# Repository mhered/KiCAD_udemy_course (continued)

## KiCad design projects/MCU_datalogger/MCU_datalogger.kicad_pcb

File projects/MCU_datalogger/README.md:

# README.md

A simple **microcontroller-based datalogger** designed to practice PCB design in KiCAD while introducing the fundamentals of embedded data acquisition. The board reads sensor data through the MCU and stores it in EEPROM, making it possible to log measurements over time.

The design covers the key building blocks of a typical datalogger system:

- **MCU (microcontroller)** – handles sensor interfacing, data collection, and storage management.
- **Sensors / Inputs** – generic sensor connections to capture physical measurements.
- **EEPROM** – nonvolatile memory to store logged data.
- **Power supply** – provides stable operation from external power or batteries.
- **Programming / Debug headers** – for uploading firmware and retrieving logged data (??)

DS1337S

ATMEGA328P-AU from SNAPEDA

## v1.0

## v1.1

Adjust edges and silkscreen, add Vcc fill zone

## Bootloading and firmware uploading the ATMEGA328

- Arduino to atmega328 [Arduino Uno to ATmega328 - Shrinking your Arduino ProjectsYouTube · DroneBot Workshop29 Dec 2018](https://www.youtube.com/watch?v=Sww1mek5rHU)
- Shrinking arduino projects atmega328 https://youtu.be/aex1HFhJG_g?si=vZYHLi1vfadTmJW0

- http://www.kerrywong.com/2010/09/25/i2c-data-logger-using-atmega328p-and-ds3232/

## v1.3

ChatGPT disagrees with the choice of an electrolytic 100nF capacitor in parallel with the battery it says it is too slow. and recommends instead a ceramic 100nF close to the MCU pins to act as filter for spikes. Optionally can add a 10-100uF bulk cap (e.g. electrolytic) to stabilize)

I cant find anything in the datasheet

Looks like EEPROM address is hardcoded 111 and 101, check datasheet!

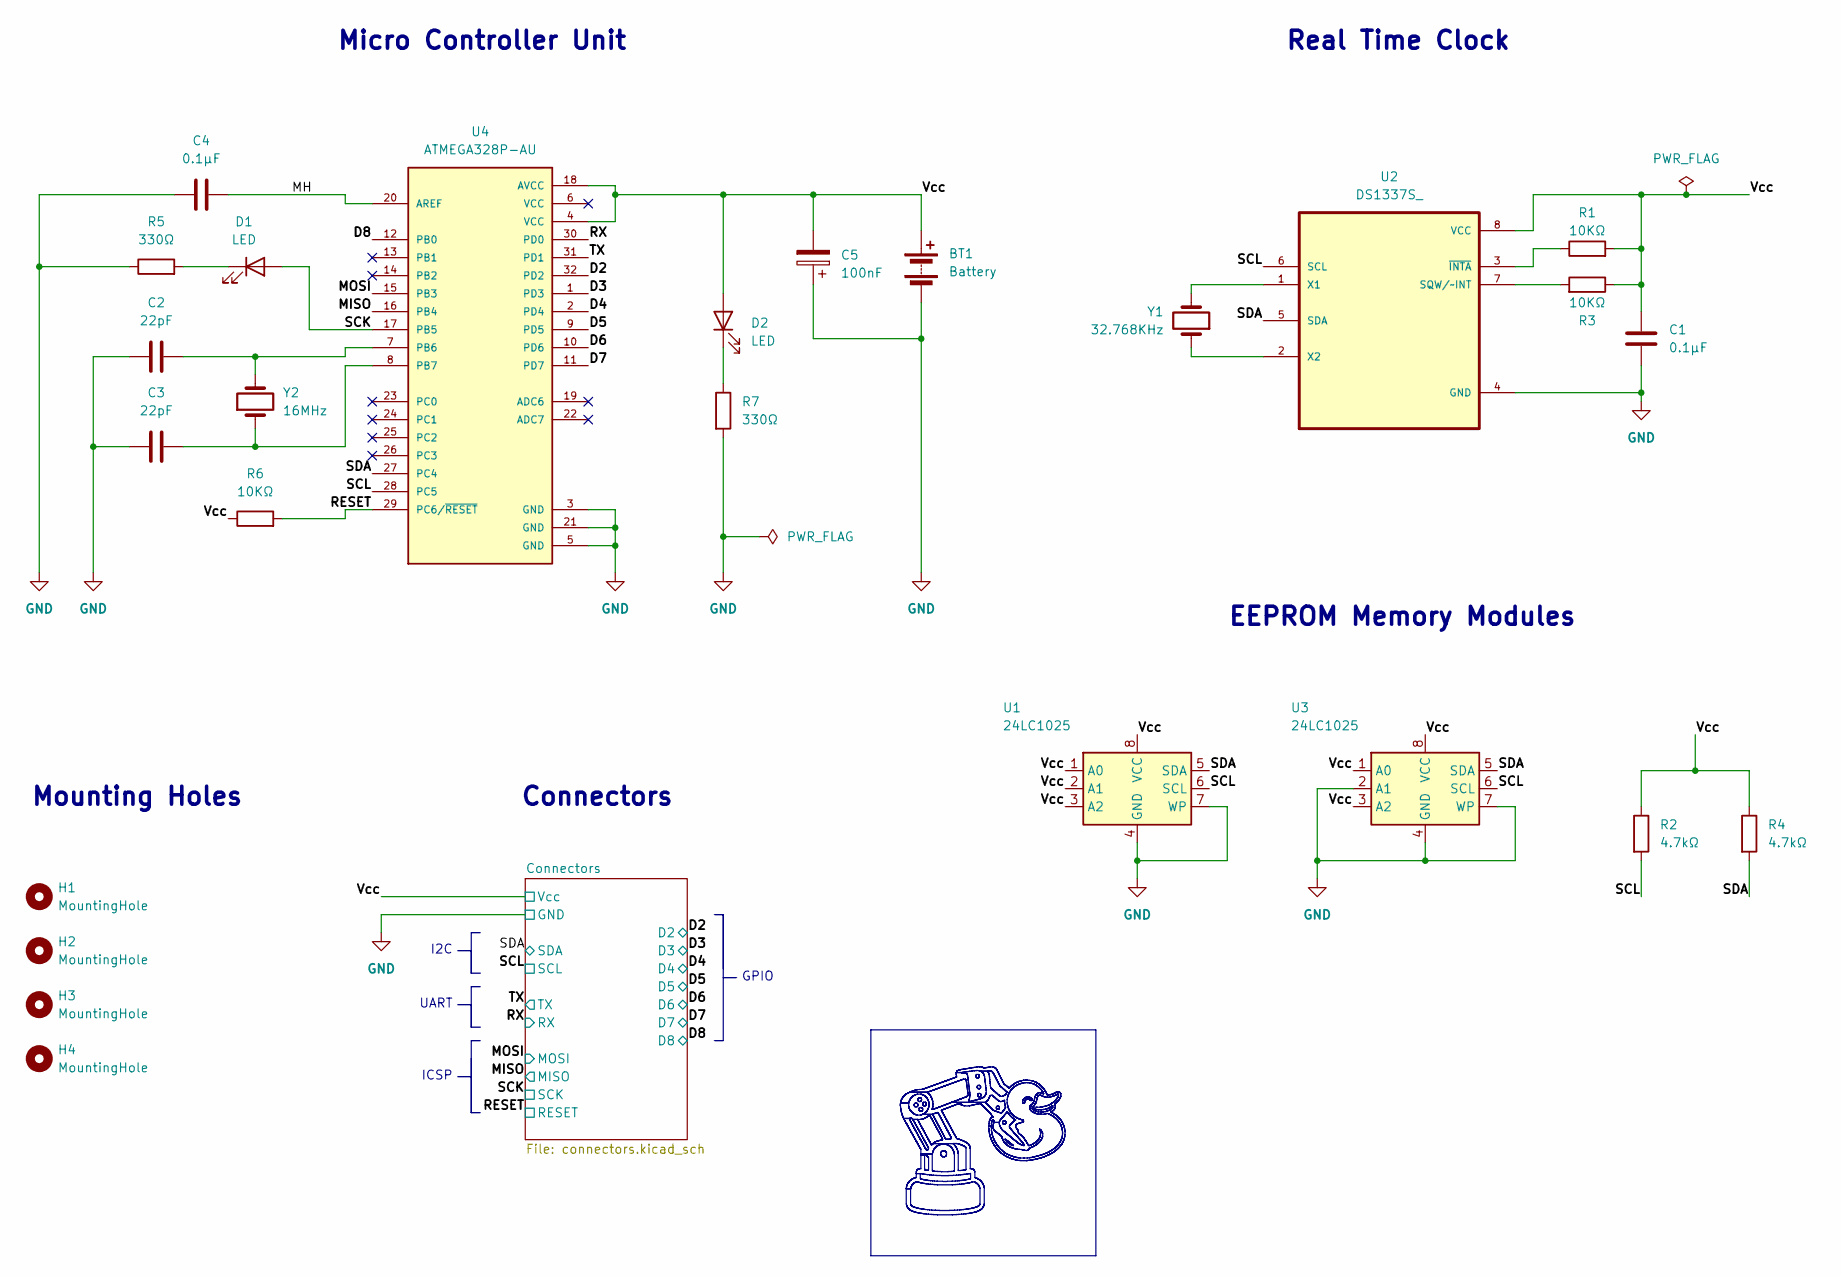
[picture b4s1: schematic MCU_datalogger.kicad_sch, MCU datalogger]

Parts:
BT1: Battery; PinHeader_1x02_P2.54mm_Vertical
C1, C4: 0.1μF; C_1206_3216Metric_Pad1.33x1.80mm_HandSolder
C2, C3: 22pF; C_1206_3216Metric_Pad1.33x1.80mm_HandSolder
C5: 100nF; C_1206_3216Metric_Pad1.33x1.80mm_HandSolder
D1, D2: LED; LED_1206_3216Metric_Pad1.42x1.75mm_HandSolder
H1, H2, H3, H4: MountingHole; MountingHole_2.2mm_M2
R1, R3, R6: 10KΩ; R_1206_3216Metric_Pad1.30x1.75mm_HandSolder
R2, R4: 4.7kΩ; R_1206_3216Metric_Pad1.30x1.75mm_HandSolder
R5, R7: 330Ω; R_1206_3216Metric_Pad1.30x1.75mm_HandSolder
U1, U3: 24LC1025; SOIC-8_5.3x5.3mm_P1.27mm
U2: DS1337S_; SOIC127P600X175-8N
U4: ATMEGA328P-AU; QFP80P900X900X120-32N; PARTREV 8271A
Y1: 32.768KHz; Crystal_SMD_3215-2Pin_3.2x1.5mm
Y2: 16MHz; Crystal_SMD_5032-2Pin_5.0x3.2mm_HandSoldering

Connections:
/D2: U4.32 (PD2); also elsewhere on the board
/D3: U4.1 (PD3); also elsewhere on the board
/D4: U4.2 (PD4); also elsewhere on the board
/D5: U4.9 (PD5); also elsewhere on the board
/D6: U4.10 (PD6); also elsewhere on the board
/D7: U4.11 (PD7); also elsewhere on the board
/D8: U4.12 (PB0); also elsewhere on the board
/MH: C4.2, U4.20 (AREF)
/MISO: U4.16 (PB4); also elsewhere on the board
/MOSI: U4.15 (PB3); also elsewhere on the board
/RESET: R6.2, U4.29 (PC6/~RESET); also elsewhere on the board
/RX: U4.30 (PD0); also elsewhere on the board
/SCK: D1.2 (A), U4.17 (PB5); also elsewhere on the board
/SCL: R2.2, U1.6 (SCL), U2.6 (SCL), U3.6 (SCL), U4.28 (PC5); also elsewhere on the board
/SDA: R4.2, U1.5 (SDA), U2.5 (SDA), U3.5 (SDA), U4.27 (PC4); also elsewhere on the board
/TX: U4.31 (PD1); also elsewhere on the board
/Vcc: BT1.1 (+), C1.1, C5.2, D2.2 (A), R1.2, R2.1, R3.1, R4.1, R6.1, U1.1 (A0), U1.2 (A1), U1.3 (A2), U1.8 (VCC), U2.8 (VCC), U3.1 (A0), U3.3 (A2), U3.8 (VCC), U4.4 (VCC), U4.18 (AVCC); also elsewhere on the board
GND: BT1.2 (-), C1.2, C2.1, C3.1, C4.1, C5.1, R5.1, R7.2, U1.4 (GND), U1.7 (WP), U2.4 (GND), U3.2 (A1), U3.4 (GND), U3.7 (WP), U4.3 (GND), U4.5 (GND), U4.21 (GND); also elsewhere on the board
unnamed: D1.1 (K), R5.2
unnamed: D2.1 (K), R7.1
unnamed: R3.2, U2.7 (SQW/~INT)
unnamed: U2.1 (X1), Y1.2
unnamed: U2.2 (X2), Y1.1
unnamed: R1.1, U2.3 (~INTA)
unnamed: C2.2, U4.7 (PB6), Y2.2
unnamed: C3.2, U4.8 (PB7), Y2.1

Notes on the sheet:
Connectors
Micro Controller Unit
EEPROM Memory Modules
UART
I2C
GPIO
Real Time Clock
Mounting Holes
ICSP

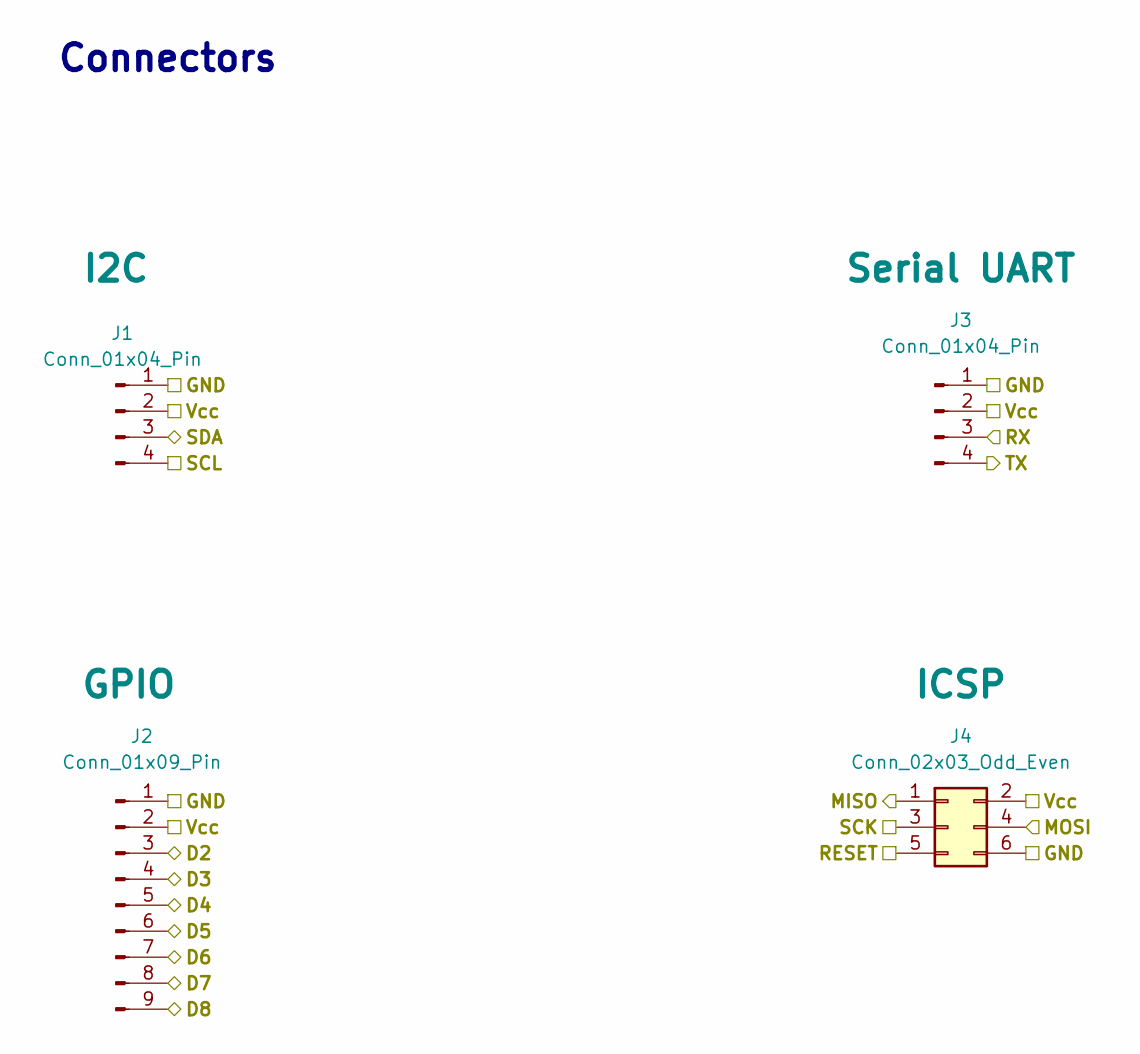
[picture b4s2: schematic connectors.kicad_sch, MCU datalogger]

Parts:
J1, J3: Conn_01x04_Pin; PinHeader_1x04_P2.54mm_Vertical
J2: Conn_01x09_Pin; PinHeader_1x09_P2.54mm_Vertical
J4: Conn_02x03_Odd_Even; PinHeader_2x03_P2.54mm_Vertical

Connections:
/D2: J2.3; also elsewhere on the board
/D3: J2.4; also elsewhere on the board
/D4: J2.5; also elsewhere on the board
/D5: J2.6; also elsewhere on the board
/D6: J2.7; also elsewhere on the board
/D7: J2.8; also elsewhere on the board
/D8: J2.9; also elsewhere on the board
/MISO: J4.1; also elsewhere on the board
/MOSI: J4.4; also elsewhere on the board
/RESET: J4.5; also elsewhere on the board
/RX: J3.3; also elsewhere on the board
/SCK: J4.3; also elsewhere on the board
/SCL: J1.4; also elsewhere on the board
/SDA: J1.3; also elsewhere on the board
/TX: J3.4; also elsewhere on the board
/Vcc: J1.2, J2.2, J3.2, J4.2; also elsewhere on the board
GND: J1.1, J2.1, J3.1, J4.6; also elsewhere on the board

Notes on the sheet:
Connectors

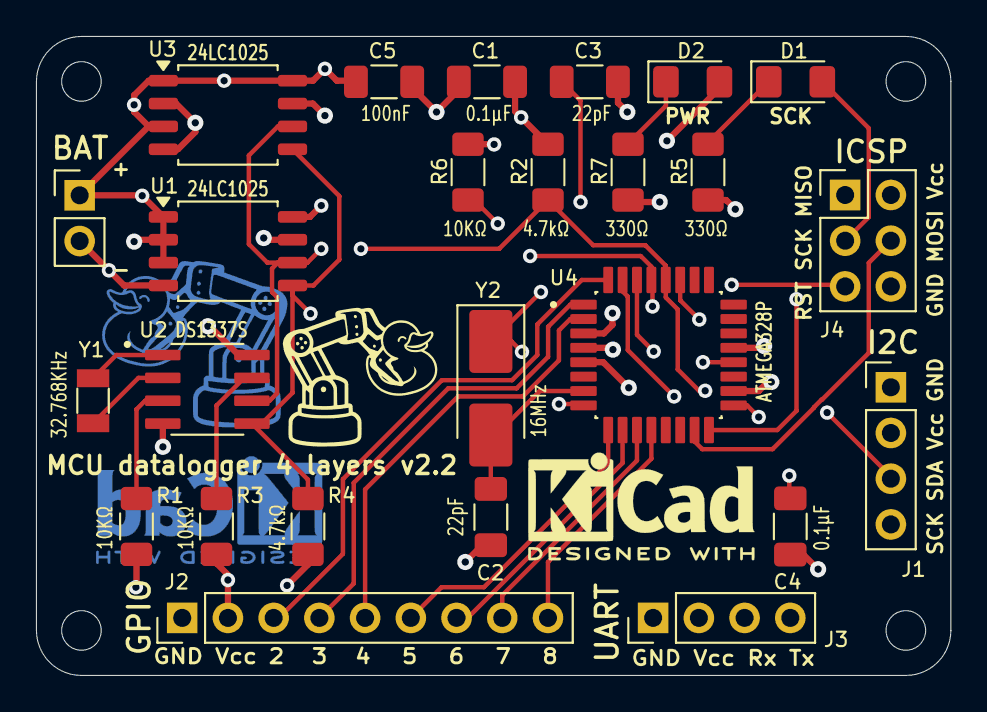
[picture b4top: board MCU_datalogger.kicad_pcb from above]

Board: 4 copper layers, 50.8 x 35.5 mm, 29 parts (0 on the bottom side), 26 nets.

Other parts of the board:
BAT: Battery; PinHeader_1x02_P2.54mm_Vertical

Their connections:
/Vcc: BAT.1 (+); also elsewhere on the board
GND: BAT.2 (-); also elsewhere on the board

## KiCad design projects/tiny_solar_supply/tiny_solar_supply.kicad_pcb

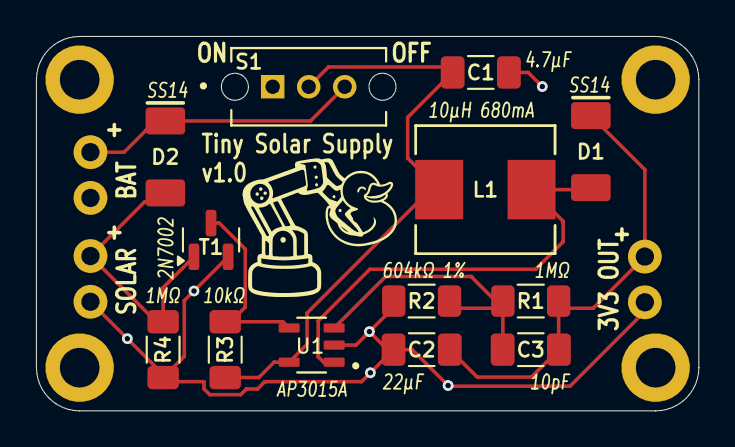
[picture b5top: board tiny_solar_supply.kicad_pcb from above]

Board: 2 copper layers, 36.8 x 20.8 mm, 16 parts (0 on the bottom side), 8 nets.

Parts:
C1: 4.7µF; C_1206_3216Metric_Pad1.33x1.80mm_HandSolder
C2: 22µF; C_1206_3216Metric_Pad1.33x1.80mm_HandSolder
C3: 10pF; C_1206_3216Metric_Pad1.33x1.80mm_HandSolder
D1, D2: SS14; SMA
J1, J2, J4: Conn_01x02; 1x02
L1: 10µH 680mA; IND_ASPI-0630LR_ABR
R1, R4: 1MΩ; R_1206_3216Metric_Pad1.30x1.75mm_HandSolder
R2: 604kΩ 1%; R_1206_3216Metric_Pad1.30x1.75mm_HandSolder
R3: 10kΩ; R_1206_3216Metric_Pad1.30x1.75mm_HandSolder
S1: OS102011MS2QN1; SW_OS102011MS2QN1
T1: 2N7002; SOT-23
U1: AP3015A; SOT95P280X145-5N

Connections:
/BATT_POSITIVE: D2.1 (K), J2.1, S1.3
/OUTPUT_POSITIVE: C2.2, C3.2, D1.1 (K), J1.1, R1.2
/SOLAR_POSITIVE: D2.2 (A), J4.1, R4.2, T1.1 (G)
GNDD: C1.1, C2.1, J1.2, J2.2, J4.2, R2.1, R4.1, T1.2 (S), U1.2 (GND)
unnamed: D1.2 (A), L1.2, U1.1 (SW)
unnamed: R3.1, T1.3 (D), U1.4 (~SHDN)
unnamed: C3.1, R1.1, R2.2, U1.3 (FB)
unnamed: C1.2, L1.1, R3.2, S1.2, U1.5 (VIN)

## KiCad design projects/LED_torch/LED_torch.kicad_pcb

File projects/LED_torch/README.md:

# README.md

## LED_torch - a first basic PCB project 

## Designing the covers

make it clip snuggly while allowing for tolerances, (especially on the soldered components) is fun

## 3D printing the covers

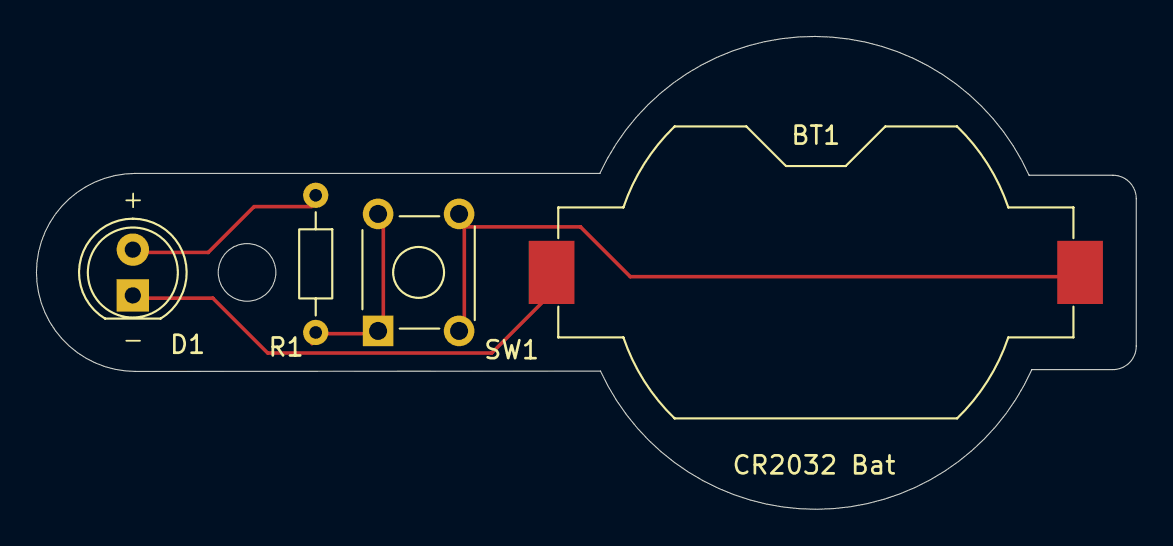
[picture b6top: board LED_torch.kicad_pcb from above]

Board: 2 copper layers, 61.1 x 26.3 mm, 4 parts (0 on the bottom side), 4 nets.

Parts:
BT1: CR2032 Bat; BatteryHolder_Keystone_1058_1x2032
D1: LED; LED_D5.0mm
R1: R; R_Axial_DIN0204_L3.6mm_D1.6mm_P7.62mm_Horizontal
SW1: SW_DPDT_x2; SW_TH_Tactile_Omron_B3F-10xx

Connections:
/LED_anode: D1.2 (A), R1.1
/LED_cathode: BT1.2 (-), D1.1 (K)
/bat_pos: BT1.1 (+), SW1.2 (B)
unnamed: R1.2, SW1.1 (A)

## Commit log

2025-07-05 Remove unnnecesary files
2025-07-05 Project 1-LED Torch v01 v02 v03 and logos
2025-07-05 Cleaned up ignored files from tracking
2025-07-06 Add 3D model for switch and BOM. Add GIF to notes.
2025-07-06 Add figure with types of pads
2025-07-06 Add figures for vias and solder paste
2025-07-06 Notes for Section 6
2025-07-06 Fix typo
2025-07-06 Improve vias.png figure - add plating
2025-07-06 Improve notes
2025-07-09 Split notes into files. Add notes of Section 7.
2025-07-23 Add notes on Schematic Editor
2025-07-23 Modify data on sheet box
2025-07-23 Add images of Schematic editor toolbars
2025-07-23 Add test project - create a custom symbol
2025-07-23 Project 2: Breadboard power supply - Initial commit
2025-08-27 Organize libraries, add footprints (WIP)
2025-08-27 Best practices for libraries in breadboard_power_supply project
    - move libraries/ folder inside main project folder
    - make paths references relative using ${KIPRJMOD} variable
    - modify .gitignore to commit fp-lib-table and sym-lib-table
    - update links to MH_Slider_Switch symbol and footprint in KiCAD files
2025-08-27 Remove unused footprint file, commit notes, update To do
2025-08-28 Complete associations, start wiring
2025-08-28 Configure Git LFS to track CAD files
2025-08-28 Move STEP file (Slide_Switch 3D model) into GIT LFS
2025-08-28 Warn about usage of GIT LFS in README.md
2025-08-28 Add LED_torch CAD files with FLS
2025-08-28 Configure Git LFS to track zipped gerbers
2025-08-28 Add LED_torch gerbers with LFS
2025-08-28 Clean up nextpcb/ folder
2025-08-28 Commit README.md figures
2025-08-28 Clean up duplicated files
2025-08-28 Add button switch CAD model with LFS
2025-08-28 Add README.md, figures and interactive BOM to kinect_lite
2025-08-28 Initial commit for project ReSkin
2025-08-28 Add component shopping lists (WIP)
2025-08-28 Add MH_Barrel_Jack library
2025-08-28 Improve notes
    - fix links
    - add link to recommended library setup notes in README.md
    - move footprint associations notes to relevant section
2025-08-29 Complete wiring
2025-09-01 Name Nets
2025-09-06 Define net classes, add text and boxes, improve logo
    - Add net classes
    - Add boxes, text, and graphics to the drawing sheet
    - improve color version of logo: blacker lines, round
    junction on the left, clean background
    - make b/w version of logo in BMP and then .kicad_mod
    using Image Converter to use as silkscreen logo
2025-09-06 Add links to figures
2025-09-17 Create Tiny Solar Supply project
2025-09-18 README and sources for tiny_solar_supply
2025-09-18 Finish breadboard_power_supply projeect in v1
    Finish PCB design
    Correct design issues in schematic and PCB: separate power_output nets A and B,
    rewire accordingly
    Add silkscreen text and decorations
    Improve 3D
    Improve notes
2025-09-18 Finish v1 of kinect_lite
    Modify silkscreen
    Add graphics to copper layer (designed wuth kicad and duckie robot)
    round corners of outline
    generate Gerbers
    Create v2 and v3 of 3D printed cover in FreeCAD
    export STL for 3D printing
2025-09-18 Add LCSC components order
2025-09-18 Move tiny_solar_supply KiCAD files
2025-09-18 Reorder kinect_lite notes, add figures
2025-09-18 Add missing CAD symbols,footprints and models
2025-09-19 Start adding symbols
2025-09-19 Add pictures to breadboard_power_supply README.md
2025-09-19 Add pictures to kinect_lite README.md
2025-09-19 Save unknown changes to STEP files (??)
2025-09-25 Initial commit of schematic
2025-09-25 Schematic - complete with ERC
2025-09-25 Layout initial commit - draft arrangement of components
2025-09-27 Complete tiny_solar_supply_ v1 PCB layout, add missing 3D models
2025-09-29 Store STEP model in Git LFS
2025-09-29 Create template project
2025-09-29 Initial commit MCU datalogger
2025-09-29 Add slide switch to tiny solar libraries
2025-09-29 Rename template -> TEMPLATE, fix graphics
2025-09-29 Add components to MCU dataloogger
2025-09-30 tiny_solar_supply_v2 PCB layout inc. mounting holes
2025-09-30 Add BOM to breadboard_power_supply
2025-09-30 Add BOM to tiny_solar_supply
2025-09-30 Add details to tiny_solar_supply
    Improve silkscreen
    add logo title and version v1.0
    replace header pins by slide switch
    NOTE: broken link to shematic (tiny_solar_supply_v2.kicad_sch does not exist!)
2025-12-21 breadboard power supply version v2.0
    Changes in v2.0 (Dec'25):
    - fix errors:
    - flip Switch S1 (so OFF and ON work as intended)
    - flip J4 Screw Terminal (so vA+ and vA- are as intended)
    - update schematics:
    - improve readability
2025-12-21 Fix kinect_JLCPCB.png image, add output of kinect-3d-view
2025-12-23 Create v1.0 - first version sent for manufacturing
    - in folder versions/ save versions v0.1 and v1.0
    - in folder gerbers/ export gerbers of version v1.0
    - in folder assets/ rename figures of v0.1 and create figures of v1.0
    - update file README.md
2025-12-24 In MCU datalogger project add sheet 'Connectors'
2025-12-26 MC_datalogger - Arrange and anotate symbols
2025-12-26 Add lock files to .gitignore (*.lck)
2025-12-26 MCU datalogger - add component values
2025-12-26 MCU datalogger - associate footprints
2026-01-01 MCU datalogger - wiring of main sheet
2026-01-01 MCU datalogger - wiring of second sheet
2026-01-02 MCU datalogger - Assign nets GND and /Vcc to net class POWER, fix ERC warnings
2026-01-02 MCU datalogger - setup PCBNew
2026-01-02 MCU datalogger - initial layout of footprints
2026-01-02 MCU datalogger - initial routing of the PCB
2026-01-02 MCU datalogger - v1.0 complete with 3D models and logos
2026-01-03 MCU datalogger - v1.1 fine-tune edges and silkscreen
2026-01-05 MCU datalogger - v1.1 add Vcc fill zone, minor routing and silkscreen details
2026-01-05 MCU datalogger v1.1 complete. Export Gerbers and update README.
2026-01-08 Create KiCAD_tutorials.md with links to future projects
2026-01-08 Pico IoT thingy - initial commit
2026-01-08 Pico IoT thingy - Add 5V to 3V3 bar
2026-01-11 Pico IoT thingy - progress on schematics
    - user-programmable button
    - RGB LED
    - DIP switch to set address
    - SPI port
    - SHT31 sensor
2026-01-12 Pico IoT thingy - complete schematics, DRC OK
2026-01-12 Pico IoT thingy - visual cleanup of schematics
2026-01-13 Pico IoT thingy - assign footprints (WIP)
2026-01-14 Pico IoT thingy - complete footprints assignment
2026-01-15 Pico IoT thingy - initial placement of components in PCB
2026-01-15 Pico IoT thingy - Flip 1x04 screw terminal to have GND on Pin 1, add 3Ds
2026-01-15 Pico IoT thingy - add links and figure of comp placement to README.md
2026-01-21 breadboard_power_supply - clean up gerbers folder
2026-01-21 Pico IoT thingy - logos and initial routing
2026-01-21 Pico IoT thingy - remove initial routing, clean up silkscreen
2026-01-23 MCU datalogger v1.2
    - fix missing Vcc label in Battery + net
    - fix the resulting violations of Vcc routing (wider tracks required)
    - reorder pins of GPIO connector to make Pin 1 is GND
    - Add silkscreen labels to connectors I2C ICSP Serial and GPIO
    - other minor adjustments to component placements and silkscreen
2026-01-23 MCU datalogger v1.2 - add logo and silkscreen at the back
2026-01-24 MCU datalogger v2.1 (4-layer) complete, export gerbers
2026-01-24 Edit .gitattributes to ignore MCU_datalogger.kicad_pcb when merging
2026-01-24 Add /MH net label to schematic
2026-01-24 MCU datalogger v2.1 (4-layer) - update PBC from schematic to bring /MH net label
2026-01-24 MCU datalogger v1.2 (2-layer) - update PBC from schematic to bring /MH net label
2026-01-24 MCU datalogger schematic - fix bug in SCL and SCK clock signals
    Rename SCK net label to SCL where appropriate in both schematic
    drawings (Root and Connectors) to fix bug where pins 17 and 28
    of the ATMEGA were incorrectly shorted because of a confusion of
    two clock different signals:
    - SCK for ICSP
    - SCL for I2C
2026-01-24 MCU datalogger v1.3 (2-layer) complete - fixes SCL/SCK bug
2026-01-25 MCU datalogger v2.2 (4-layer) complete - fixes SCL/SCK bug
2026-01-26 Fix: store gerber ZIP MCU_datalogger_4-layer_v2.1.zip via Git LFS
2026-01-26 MCU datalogger v1.3 (2-layer) - silkscreen improvements, plot gerbers
2026-01-26 MCU datalogger v2.2 (4-layer) - silkscreen improvements, plot gerbers
2026-01-27 Pico IoT thingy v1.0 complete
2026-03-03 Pico IoT thingy v1.2 complete - 1st proto sent to production
2026-03-03 MCU datalogger - Add notes on ATMega328 programming
2026-03-03 MSPM0 - Initial commit
2026-03-11 tiny_solar_supply v1.1 initial commit
    - improve silkscreen: whit bkg on user labels
    - improve routing: vias to GND plane
    - add datasheets of AP3015 and L1
    - fix switch ON/OFF labels (were reversed)
    Pending: Fix wrong L1 footprint.
2026-03-11 pico_IoT_thingy v1.3 Initial commit - fixes after testing 1st proto
2026-03-17 MCU datalogger - add BOM, modify polarized cap, add datasheets
2026-03-18 MSPM0 - schematics up to power rail
2026-04-03 Add IMU and magnetometer (WIP)
2026-04-03 Rename project folders. Add reskin.gif. Add table of projects to main README.md
2026-04-03 MSPM0 - migrate to KiCad 10, clean up schematic
2026-04-04 MSPM0 - Complete schematic, pass ERC checks, import footprints to PCB.
2026-04-04 MSPM0 - initialize PCB layout
2026-05-02 MSPM0 - Reassign pins. Add QWIIC connector for I2C. Finish placement.
2026-05-02 MCU_datalogger - Add notes on physical board early tests
2026-05-02 MCU datalogger - clean up schematic
    In `MCU_datalogger.kicad_sch` and `connectors.kicad_sch`:
    - update RTC, EEPROM, Crystal symbols to arrange pins properly
    and align to 100 mil grid
    - clean up schematic
    - rename nets to start with ICSP_* I2C_* UART_*
    - replace Vcc label with VCC power symbol
2026-06-16 pico_Iot_thingy - Replace pico by picoW pinout diagram
2026-06-16 pico_IoT_thingy - add notes on layout v1.4
2026-06-18 pico_IoT_thingy - v1.2 testing firmware and findings
    - update README.md file with notes on testing (implementation notes + findings)
    - add several pictures to illustrate README.md file to assets/ folder
    - New Micropython/ folder contains a simple, single-pass test suite that
    validates GPIO routing, buses, sensors, and connectors immediately after PCB
    assembly.
    - README.md - firmware notes
2026-06-18 pico_IoT_thingy - add fake_picoW/ folder with firmware for fake USB-C PicoW boards without CYW43 chip
2026-06-19 pico_IoT_thingy - Migrate to KiCad 10
2026-06-19 pico_IoT_thingy - v1.4 WIP: add notes and replace LED symbol on schematic, improve labels
    Schematic:
    - add notes on:
    - U1: input voltage nominal 12V and range 6.5-36V
    - JP1: effect on SH31 I2C address
    - IC1: tying SHDN and RE to HIGH to enable auto-direction of RS485 transceiver
    - J7: jumper to enable termination resistor
